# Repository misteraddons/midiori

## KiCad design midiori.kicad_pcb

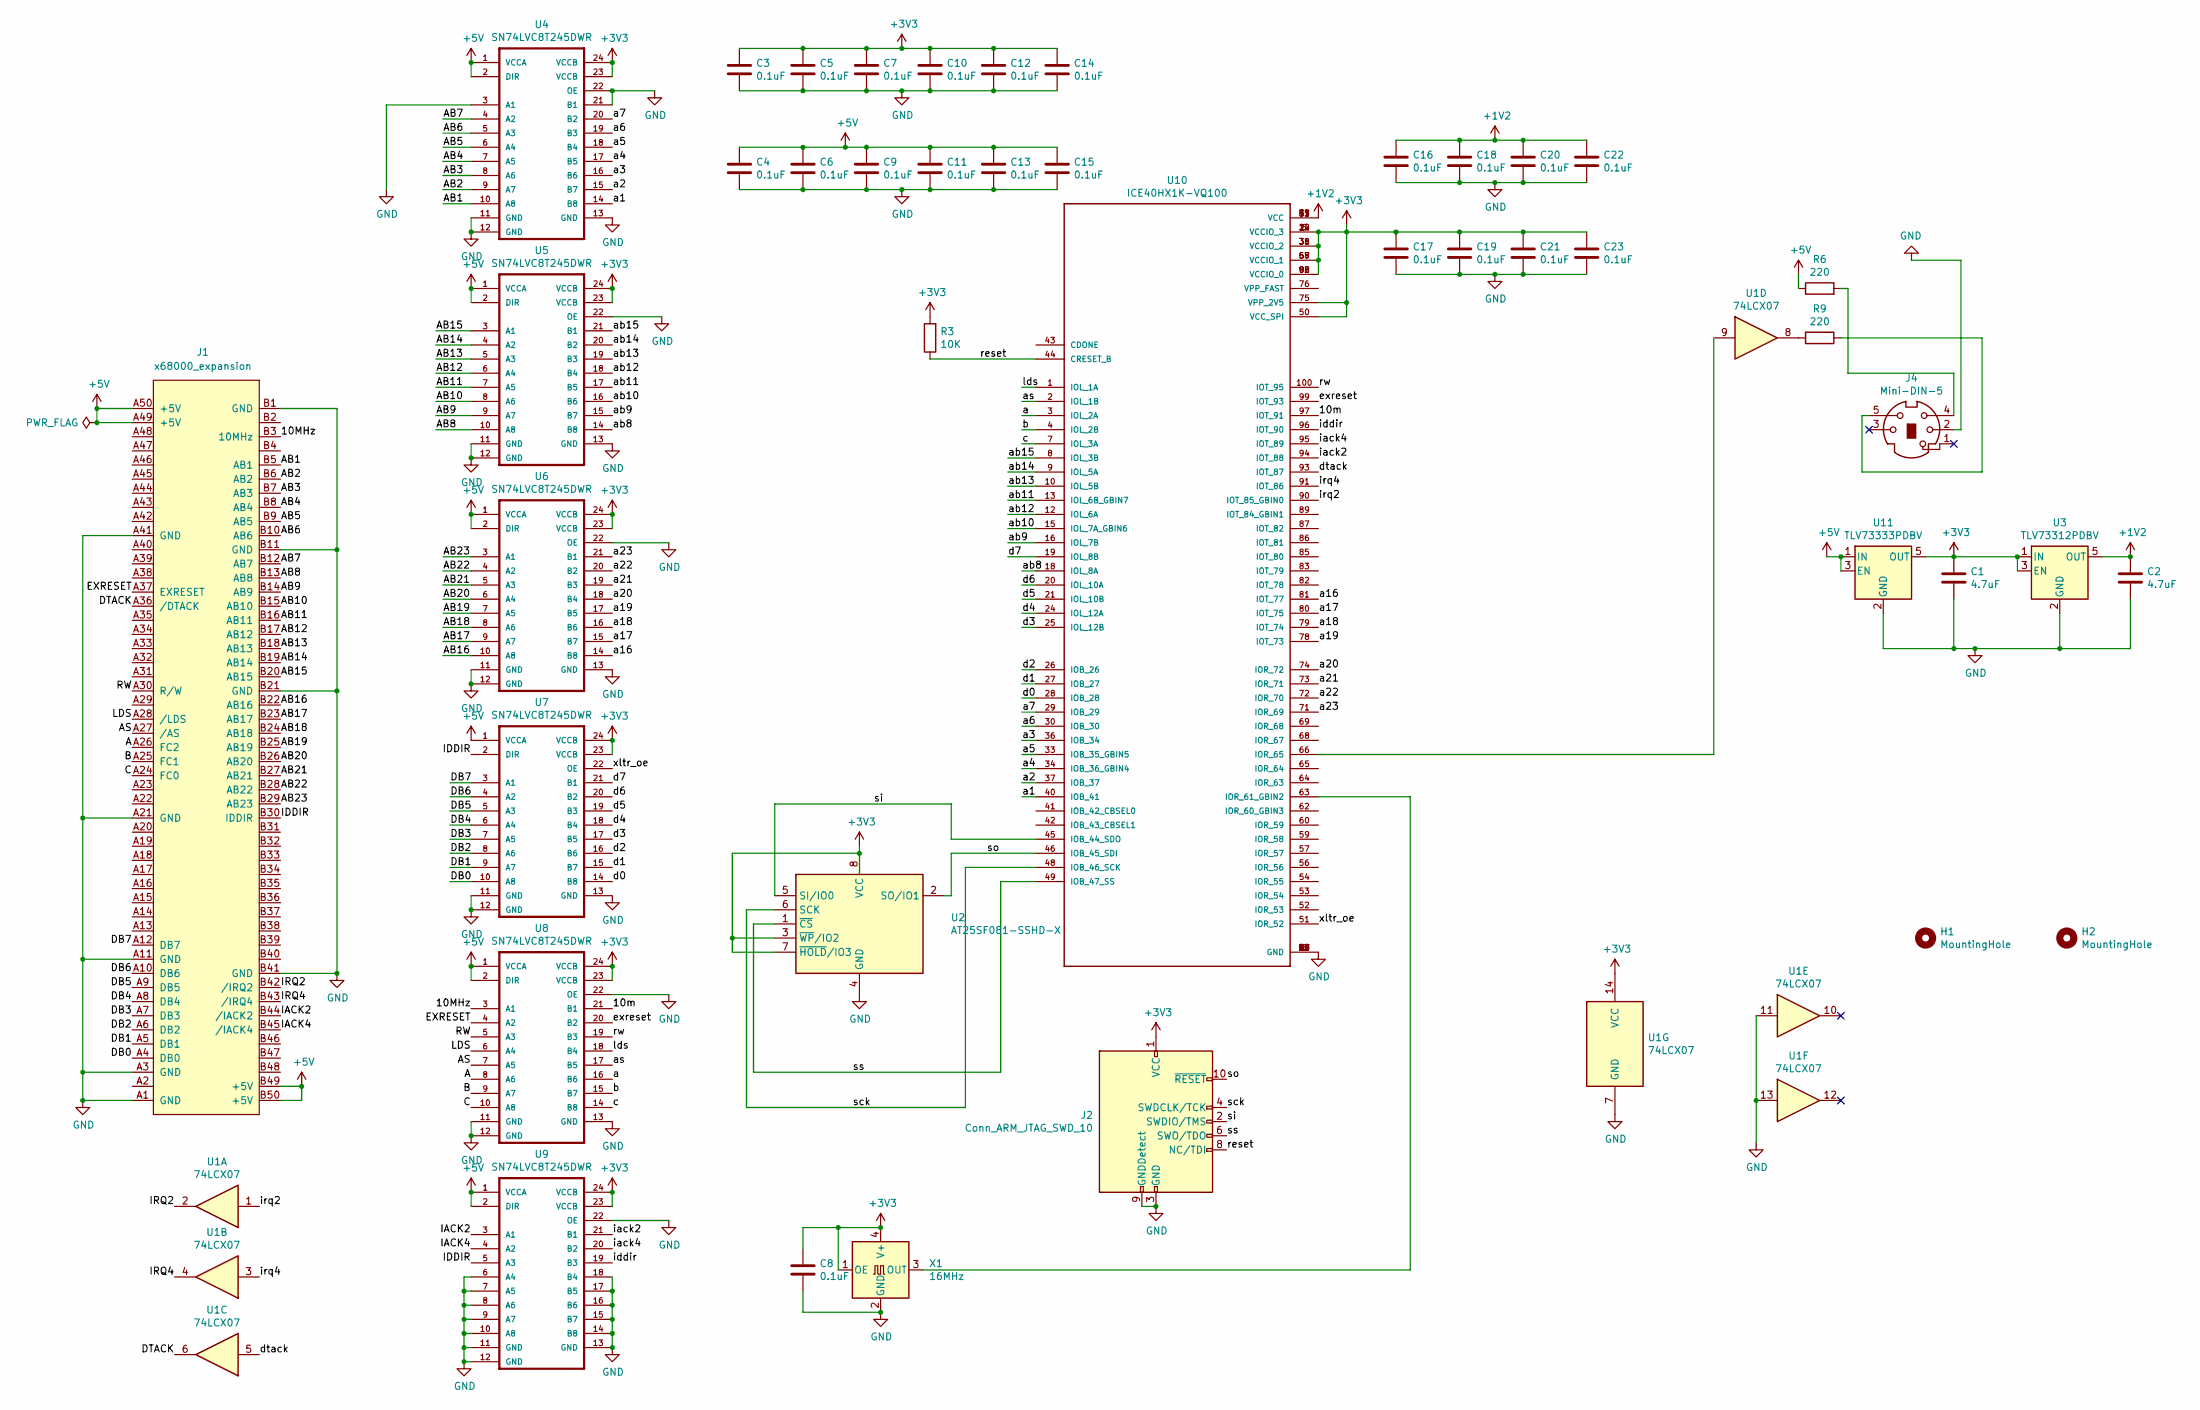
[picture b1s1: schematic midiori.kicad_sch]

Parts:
C1, C2: 4.7uF; C_0805_2012Metric; LCSC Part C1779
C3, C4, C5, C6, C7, C8, C9, C10, C11, C12, C13, C14, C15, C16, C17, C18, C19, C20, C21, C22, C23: 0.1uF; C_0805_2012Metric; LCSC Part C49678
H1, H2: MountingHole; MountingHole_3.2mm_M3_Pad
J1: x68000_expansion
J2: Conn_ARM_JTAG_SWD_10; PinHeader_2x05_P1.27mm_Vertical_SMD; LCSC Part C2935458
J4: Mini-DIN-5; MD-50SM; LCSC Part C2939346
R3: 10K; R_0805_2012Metric; LCSC Part C17414
R6, R9: 220; R_0805_2012Metric_Pad1.15x1.40mm_HandSolder; LCSC Part C17557
U1: 74LCX07; TSSOP-14_4.4x5mm_P0.65mm; LCSC Part C6006
U2: AT25SF081-SSHD-X; SOIC-8_3.9x4.9mm_P1.27mm; LCSC Part C169368
U3: TLV73312PDBV; SOT-23-5; LCSC Part C473364
U4, U5, U6, U7, U8, U9: SN74LVC8T245DWR; SOIC-24W_7.5x15.4mm_P1.27mm; LCSC Part C2677350
U10: ICE40HX1K-VQ100; QFP50P1600X1600X120-100N; LCSC Part C1519043
U11: TLV73333PDBV; SOT-23-5; LCSC Part C134139
X1: 16MHz; Oscillator_SMD_SeikoEpson_SG8002CA-4Pin_7.0x5.0mm; LCSC Part C386990

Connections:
+1V2: C2.1, C16.1, C18.1, C20.1, C22.1, U3.5 (OUT), U10.11 (VCC), U10.35 (VCC), U10.61 (VCC), U10.77 (VCC)
+3V3: C1.1, C3.1, C5.1, C7.1, C8.1, C10.1, C12.1, C14.1, C17.1, C19.1, C21.1, C23.1, J2.1 (VCC), R3.2, U1.14 (VCC), U2.3 (~WP/IO2), U2.7 (~HOLD/IO3), U2.8 (VCC), U3.1 (IN), U3.3 (EN), U4.23 (VCCB), U4.24 (VCCB), U5.23 (VCCB), U5.24 (VCCB), U6.23 (VCCB), U6.24 (VCCB), U7.23 (VCCB), U7.24 (VCCB), U8.23 (VCCB), U8.24 (VCCB), U9.23 (VCCB), U9.24 (VCCB), U10.6 (VCCIO_3), U10.14 (VCCIO_3), U10.22 (VCCIO_3), U10.31 (VCCIO_2), U10.38 (VCCIO_2), U10.50 (VCC_SPI), U10.58 (VCCIO_1), U10.67 (VCCIO_1), U10.75 (VPP_2V5), U10.88 (VCCIO_0), U10.92 (VCCIO_0), U11.5 (OUT), X1.1 (OE), X1.4 (V+)
+5V: C4.1, C6.1, C9.1, C11.1, C13.1, C15.1, J1.A49 (+5V), J1.A50 (+5V), J1.B49 (+5V), J1.B50 (+5V), R6.1, U4.1 (VCCA), U4.2 (DIR), U5.1 (VCCA), U5.2 (DIR), U6.1 (VCCA), U6.2 (DIR), U7.1 (VCCA), U8.1 (VCCA), U8.2 (DIR), U9.1 (VCCA), U9.2 (DIR), U11.1 (IN), U11.3 (EN)
/10MHz: J1.B3 (10MHz), U8.3 (A1)
/10m: U8.21 (B1), U10.97 (IOT_91)
/A: J1.A26 (FC2), U8.8 (A6)
/AB1: J1.B5 (AB1), U4.10 (A8)
/AB2: J1.B6 (AB2), U4.9 (A7)
/AB3: J1.B7 (AB3), U4.8 (A6)
/AB4: J1.B8 (AB4), U4.7 (A5)
/AB5: J1.B9 (AB5), U4.6 (A4)
/AB6: J1.B10 (AB6), U4.5 (A3)
/AB7: J1.B12 (AB7), U4.4 (A2)
/AB8: J1.B13 (AB8), U5.10 (A8)
/AB9: J1.B14 (AB9), U5.9 (A7)
/AB10: J1.B15 (AB10), U5.8 (A6)
/AB11: J1.B16 (AB11), U5.7 (A5)
/AB12: J1.B17 (AB12), U5.6 (A4)
/AB13: J1.B18 (AB13), U5.5 (A3)
/AB14: J1.B19 (AB14), U5.4 (A2)
/AB15: J1.B20 (AB15), U5.3 (A1)
/AB16: J1.B22 (AB16), U6.10 (A8)
/AB17: J1.B23 (AB17), U6.9 (A7)
/AB18: J1.B24 (AB18), U6.8 (A6)
/AB19: J1.B25 (AB19), U6.7 (A5)
/AB20: J1.B26 (AB20), U6.6 (A4)
/AB21: J1.B27 (AB21), U6.5 (A3)
/AB22: J1.B28 (AB22), U6.4 (A2)
/AB23: J1.B29 (AB23), U6.3 (A1)
/AS: J1.A27 (/AS), U8.7 (A5)
/B: J1.A25 (FC1), U8.9 (A7)
/C: J1.A24 (FC0), U8.10 (A8)
/DB0: J1.A4 (DB0), U7.10 (A8)
/DB1: J1.A5 (DB1), U7.9 (A7)
/DB2: J1.A6 (DB2), U7.8 (A6)
/DB3: J1.A7 (DB3), U7.7 (A5)
/DB4: J1.A8 (DB4), U7.6 (A4)
/DB5: J1.A9 (DB5), U7.5 (A3)
/DB6: J1.A10 (DB6), U7.4 (A2)
/DB7: J1.A12 (DB7), U7.3 (A1)
/DTACK: J1.A36 (/DTACK), U1.6
/EXRESET: J1.A37 (EXRESET), U8.4 (A2)
/IACK2: J1.B44 (/IACK2), U9.3 (A1)
/IACK4: J1.B45 (/IACK4), U9.4 (A2)
/IDDIR: J1.B30 (IDDIR), U7.2 (DIR), U9.5 (A3)
/IRQ2: J1.B42 (/IRQ2), U1.2
/IRQ4: J1.B43 (/IRQ4), U1.4
/LDS: J1.A28 (/LDS), U8.6 (A4)
/RW: J1.A30 (R/W), U8.5 (A3)
/a: U8.16 (B6), U10.3 (IOL_2A)
/a1: U4.14 (B8), U10.40 (IOB_41)
/a2: U4.15 (B7), U10.37 (IOB_37)
/a3: U4.16 (B6), U10.36 (IOB_34)
/a4: U4.17 (B5), U10.34 (IOB_36_GBIN4)
/a5: U4.18 (B4), U10.33 (IOB_35_GBIN5)
/a6: U4.19 (B3), U10.30 (IOB_30)
/a7: U4.20 (B2), U10.29 (IOB_29)
/a16: U6.14 (B8), U10.81 (IOT_77)
/a17: U6.15 (B7), U10.80 (IOT_75)
/a18: U6.16 (B6), U10.79 (IOT_74)
/a19: U6.17 (B5), U10.78 (IOT_73)
/a20: U6.18 (B4), U10.74 (IOR_72)
/a21: U6.19 (B3), U10.73 (IOR_71)
/a22: U6.20 (B2), U10.72 (IOR_70)
/a23: U6.21 (B1), U10.71 (IOR_69)
/ab8: U5.14 (B8), U10.18 (IOL_8A)
/ab9: U5.15 (B7), U10.16 (IOL_7B)
/ab10: U5.16 (B6), U10.15 (IOL_7A_GBIN6)
/ab11: U5.17 (B5), U10.13 (IOL_6B_GBIN7)
/ab12: U5.18 (B4), U10.12 (IOL_6A)
/ab13: U5.19 (B3), U10.10 (IOL_5B)
/ab14: U5.20 (B2), U10.9 (IOL_5A)
/ab15: U5.21 (B1), U10.8 (IOL_3B)
/as: U8.17 (B5), U10.2 (IOL_1B)
/b: U8.15 (B7), U10.4 (IOL_2B)
/c: U8.14 (B8), U10.7 (IOL_3A)
/d0: U7.14 (B8), U10.28 (IOB_28)
/d1: U7.15 (B7), U10.27 (IOB_27)
/d2: U7.16 (B6), U10.26 (IOB_26)
/d3: U7.17 (B5), U10.25 (IOL_12B)
/d4: U7.18 (B4), U10.24 (IOL_12A)
/d5: U7.19 (B3), U10.21 (IOL_10B)
/d6: U7.20 (B2), U10.20 (IOL_10A)
/d7: U7.21 (B1), U10.19 (IOL_8B)
/dtack: U1.5, U10.93 (IOT_87)
/exreset: U8.20 (B2), U10.99 (IOT_93)
/iack2: U9.21 (B1), U10.94 (IOT_88)
/iack4: U9.20 (B2), U10.95 (IOT_89)
/iddir: U9.19 (B3), U10.96 (IOT_90)
/irq2: U1.1, U10.90 (IOT_85_GBIN0)
/irq4: U1.3, U10.91 (IOT_86)
/lds: U8.18 (B4), U10.1 (IOL_1A)
/reset: J2.8 (NC/TDI), R3.1, U10.44 (CRESET_B)
/rw: U8.19 (B3), U10.100 (IOT_95)
/sck: J2.4 (SWDCLK/TCK), U2.6 (SCK), U10.48 (IOB_46_SCK)
/si: J2.2 (SWDIO/TMS), U2.5 (SI/IO0), U10.45 (IOB_44_SDO)
/so: J2.10 (~RESET), U2.2 (SO/IO1), U10.46 (IOB_45_SDI)
/ss: J2.6 (SWO/TDO), U2.1 (~CS), U10.49 (IOB_47_SS)
/xltr_oe: U7.22 (OE), U10.51 (IOR_52)
GND: C1.2, C2.2, C3.2, C4.2, C5.2, C6.2, C7.2, C8.2, C9.2, C10.2, C11.2, C12.2, C13.2, C14.2, C15.2, C16.2, C17.2, C18.2, C19.2, C20.2, C21.2, C22.2, C23.2, J1.A1 (GND), J1.A3 (GND), J1.A11 (GND), J1.A21 (GND), J1.A41 (GND), J1.B1 (GND), J1.B11 (GND), J1.B21 (GND), J1.B41 (GND), J2.3 (GND), J2.5 (GND), J2.9 (GNDDetect), J4.2, U1.7 (GND), U1.11, U1.13, U2.4 (GND), U3.2 (GND), U4.3 (A1), U4.11 (GND), U4.12 (GND), U4.13 (GND), U4.21 (B1), U4.22 (OE), U5.11 (GND), U5.12 (GND), U5.13 (GND), U5.22 (OE), U6.11 (GND), U6.12 (GND), U6.13 (GND), U6.22 (OE), U7.11 (GND), U7.12 (GND), U7.13 (GND), U8.11 (GND), U8.12 (GND), U8.13 (GND), U8.22 (OE), U9.6 (A4), U9.7 (A5), U9.8 (A6), U9.9 (A7), U9.10 (A8), U9.11 (GND), U9.12 (GND), U9.13 (GND), U9.14 (B8), U9.15 (B7), U9.16 (B6), U9.17 (B5), U9.18 (B4), U9.22 (OE), U10.5 (GND), U10.17 (GND), U10.23 (GND), U10.32 (GND), U10.39 (GND), U10.47 (GND), U10.55 (GND), U10.70 (GND), U10.84 (GND), U10.98 (GND), U11.2 (GND), X1.2 (GND)
unnamed: J4.4, R6.2
unnamed: J4.5, R9.1
unnamed: R9.2, U1.8
unnamed: U1.9, U10.66 (IOR_65)
unnamed: U10.63 (IOR_61_GBIN2), X1.3 (OUT)

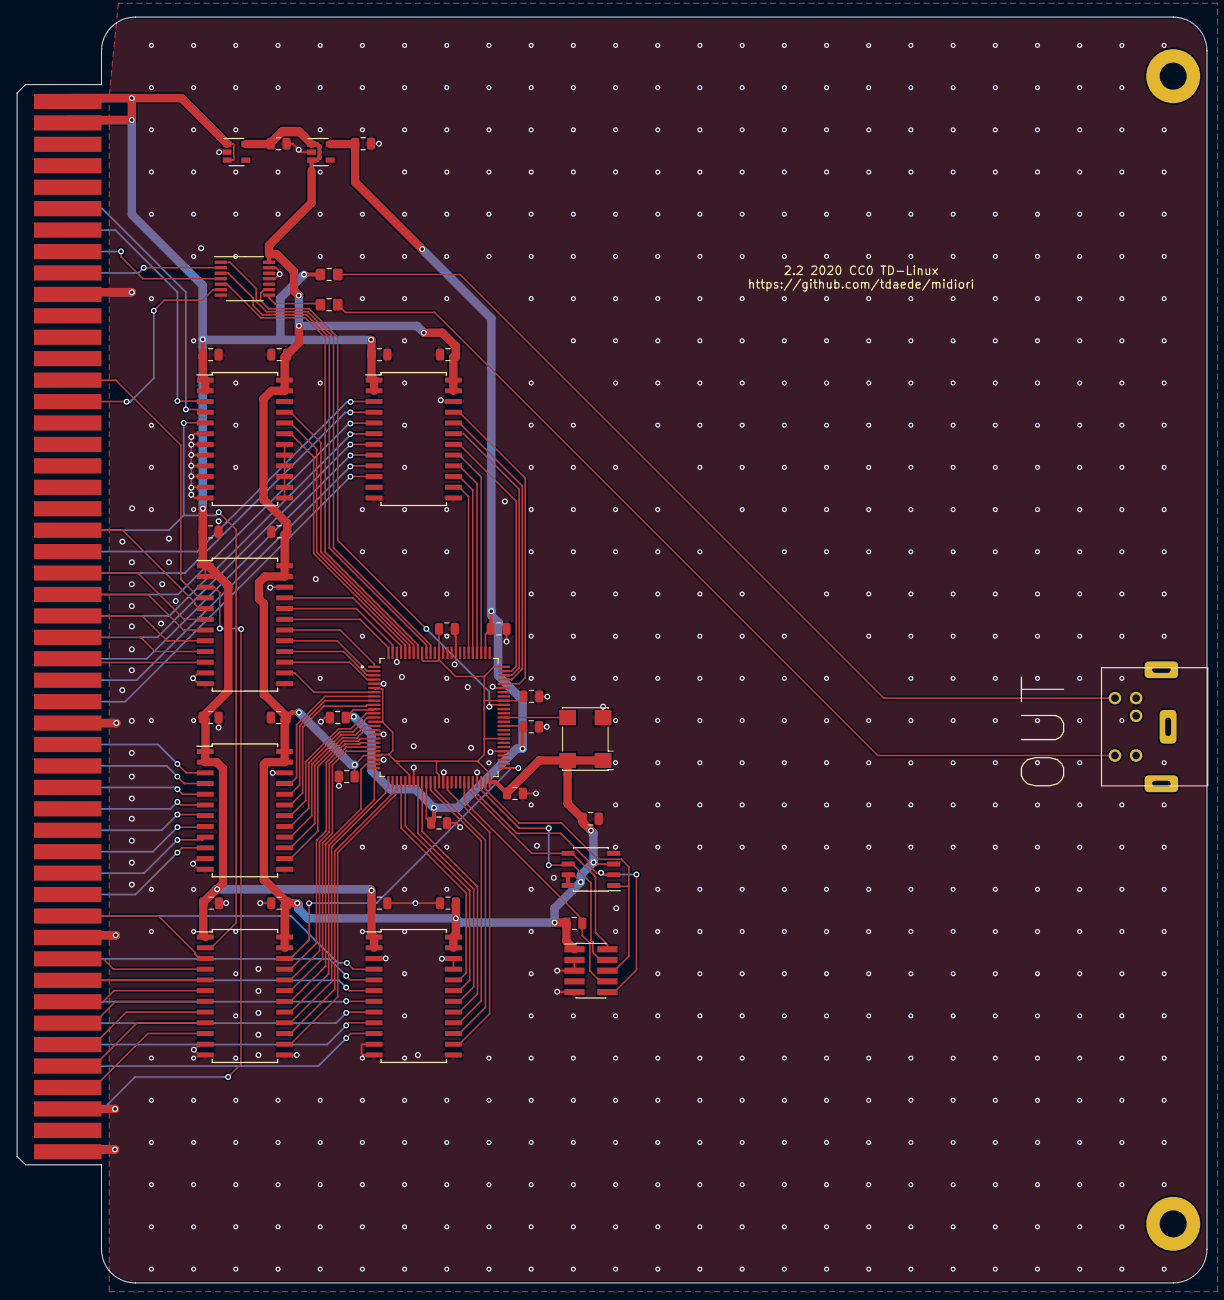
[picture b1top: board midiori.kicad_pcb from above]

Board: 2 copper layers, 141.0 x 150.0 mm, 43 parts (0 on the bottom side), 105 nets.

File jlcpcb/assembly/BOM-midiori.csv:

Comment,Designator,Footprint,LCSC
TLV73333PDBV,U11,SOT-23-5,C134139
ICE40HX1K-VQ100,U10,QFP50P1600X1600X120-100N,C1519043
AT25SF081-SSHD-X,U2,SOIC-8_3.9x4.9mm_P1.27mm,C169368
10K,R3,R_0805_2012Metric,C17414
220,"R6,R9",R_0805_2012Metric_Pad1.15x1.40mm_HandSolder,C17557
4.7uF,"C1,C2",C_0805_2012Metric,C1779
SN74LVC8T245DWR,"U4,U5,U6,U7,U8,U9",SOIC-24W_7.5x15.4mm_P1.27mm,C2677350
Conn_ARM_JTAG_SWD_10,J2,PinHeader_2x05_P1.27mm_Vertical_SMD,C2935458
Mini-DIN-5,J4,MD-50SM,C2939346
16MHz,X1,Oscillator_SMD_SeikoEpson_SG8002CA-4Pin_7.0x5.0mm,C386990
TLV73312PDBV,U3,SOT-23-5,C473364
0.1uF,"C10,C11,C12,C13,C14,C15,C16,C17,C18,C19,C20,C21,C22,C23,C3,C4,C5,C6,C7,C8,C9",C_0805_2012Metric,C49678
74LCX07,U1,TSSOP-14_4.4x5mm_P0.65mm,C6006
x68000_expansion,J1,x68000_expansion,
MountingHole,H2,MountingHole_3.2mm_M3_Pad,
MountingHole,H1,MountingHole_3.2mm_M3_Pad,

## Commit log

2022-10-03 Update and Refine
    Tweak routing
    1mm power traces
    Shorter ground traces
    Stitching vias
    JLCPCB ready
    Updated some footprints

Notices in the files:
midiori.kicad_pcb:
2.2 2020 CC0 TD-Linux
